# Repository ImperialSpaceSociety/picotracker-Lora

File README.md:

# Pico Ballon Tracker using LoRaWAN

## Objectives
This Pico balloon tracker is a new version to be designed by Imperial College Space Society. It is intended to offer an easy to build and low cost entry for people who want to launch small Helium filled balloons with a small tracking payload while using the Things Network LoRaWAN Network to receive the telemetry data from the balloon.

 implentation objective is to fly a small balloon around the world and to track it using the Things Network and HabHub.

## Major components
We have settled on the following components to go on the tracker solution. 

### Tracker

* Murata ABZ LoRa Module MCU with 868MHz LoRaWAN Radio and 32 Bit ARM CPU
* Ublox Max M8Q GPS module
* MS8607 Pressure temp humidity sensor
* Solar Power Management
* Possible small Energy storage by battery or super capacitor
The moto: KEEP IT SIMPLE

### TTN2HabHub Bridge

* Subscribe to Things Network Application for data from trackers
* Store Tracker data and meta data showing gateway information
* Forward tracking data to HabHub
* Possibly send data back to tracker
The bridge can be found in a seperate repo: [link](https://github.com/ImperialSpaceSociety/ttnhabbridge)

### Launch Gateway

* Portable Things Network LoRaWAN Gateway
* Cellular Internet Access to Things Network
* GPS
* Local Gateway Status Display
* Local Payload Data display

### Balloon

* Low cost 36 inch super pressure balloon
* Prestressed
* Helium Filled

### Tracker Firmware
All firmware used in the trackers can be found here: https://github.com/ImperialSpaceSociety/LoRaMac-node. Its a fork of the Semtech Loramac-node reference firmware.
Note that the code in the current repo is no longer used and is used for reference only.

# Flights
* ICSPACE15: [Flight report](https://www.union.ic.ac.uk/guilds/icseds/2020/01/long-range-lora-balloon-tracker-launch-from-london/)
* ICSPACE16: [Flight report](https://www.union.ic.ac.uk/guilds/icseds/2020/02/balloon-flights-to-austria-and-slovakia/)
* ICSPACE17: [Flight report](https://www.union.ic.ac.uk/guilds/icseds/2020/02/balloon-flights-to-austria-and-slovakia/)
* ICSPACE18: Was lost after launch
* ICSPACE19: [Flight report](https://www.union.ic.ac.uk/guilds/icseds/2020/03/launch-of-icspace19/)
* ICSPACE20 & 21: [Flight report](https://www.union.ic.ac.uk/guilds/icseds/2020/10/icspace21-flight-to-japan-and-icspace20/)
* ICSPACE22: [Flight report](https://www.union.ic.ac.uk/guilds/icseds/2020/12/first-unconfirmed-circumnavigation-of-the-earth-by-ic-space-society-balloon-icspace22/)
* ICSPACE23: [Flight report](https://www.union.ic.ac.uk/guilds/icseds/2020/12/icspace23-launch/)

Past flight paths may be viewed on the [map](https://charts.mongodb.com/charts-project-0-wlibw/public/dashboards/487e7641-c649-4822-abc5-f70eb2e155c7).

# Design Files
The PCBs are designed with Kicad and the latest designs can be found in the [hardware folder](hardware/Kicad/). We have two designs, the a and the b variant. a variant is a fully solar powered tracker with no power storage. The solar cells are directly wired to VCC and GND to power all components. b variant has a 50mAh lipo on board for power storage. The MPPT IC on board, the SPV1040, extracts maximum current from the cells to charge the battery.

As of 29/12/2020, the latest flight proven design is V1.3a. The b variant has not been flown yet.

The schematic of v1.3a is here:

Assembled tracker:

PCB top layer(v1.3a): 

PCB bottom layer(v1.3a):

# Software
We use the KEIL IDE to program the tracker. KEIL can be downloaded and used free of charge for the STM32L0 series of microcontrollers. You will be able to download Keil from [here](https://www2.keil.com/stmicroelectronics-stm32/mdk). Make sure you activate the licence so that you can compile files greater than 30kb of flash. There is no cost for the licence.

We use the ST link to program the STM32L0 microncontroller. You will likely need the ST-link Driver, which can be downloaded from their website: [link]( https://www.st.com/en/development-tools/stsw-link009.html#get-software)

To get the picotracker firmware, run the following to clone the repo. Useful tip: Ensure the repo is cloned to the root folder e.g. `C:\` because there have been issues with the path lengths of the files getting too long for Windows to handle. The repo has very very long paths, a legacy of the LoRaWAN firmware stack by STMicroelectronics.
```bash
git clone https://github.com/ImperialSpaceSociety/picotracker-Lora.git
```
The software on the latest tracker can be found in the [Software folder](Software). You need to navigate to ``Software/Projects/B-L072Z-LRWAN1/Applications/LoRa/End_Node/MDK-ARM/`` and you can open the KEIL project by clicking ``Lora.uvprojx``

Once you open Keil, it should look like this. Ensure that the 1.3a_variant of the code is selected(highlighted in picture): 

You will have to tell Keil that you are using the ST-link programmer. To do that, go to the `flash` drop down menu and select `Configure Flash Tools`. Then switch to the `debug` tab and ensure the drop down menu is set to `St-Link Debugger` as shown in the picture below. Then click the `settings` button.

When you open up the settings menu, it should look like this: 

Now that your st-link debugger is setup, its time to compile and program. Ensure the ST-link programmer is connected to the tracker, and hit compile and then upload or debug. Note: Its necessary to compile before uploading, or it will not have the latest hex file to flash to the tracker.

# Software overview
The picotracker state machine is as follows: 
It gets a GPS fix every 2 minutes and transmits it to ground

### Edits done over the reference version by STMicroelectronics
* Switching LoRaMAC regional settings depending on where it is
* Reduce tx power over US915/AU915
* Prevent sending empty frame after boot
* Use subband of 8 channels for US915/AU915
* Seperate credentials for each region of the world. 
* Prevent sticky uplinks after receiving channel change requests. Actually prevent any uplinks to test channel change requests. Wait till the next scheduled uplink.
* Different datarate for each region
* Polling specific date ranges for eeprom records
* 
# Photos
These are photos of ICSPACE19 before launch, during testing in the sun. It is a 1.1a variant, with no power storage.

# Instructions for special tests of multiregion Lorawan

In this test, I want to test if the tracker will work properly over US915. We have had issues where some packets over Canada contained no payload data. I don't know the root cause. Could be power supply issues. To narrow down causes, I have created this test, to be run on the B-L072Z-LRWAN1.

This test will:
1. transmit every 2 minutes
2. a packet the size of our typical message
3. on US915 frequencies.

I want to find out if we receive any empty packets.

## How to run the program

Clone this project and switch to branch `multi-region-tests`. All tests on multi region lorawan will be here.
Navigate to `picotracker-Lora/Software/Projects/B-L072Z-LRWAN1/Applications/LoRa/End_Node/MDK-ARM/` and run `Lora.uvprojx` with Keil.

After opening the Keil project, switch the firmware config to work on the B-L072Z-LRWAN1 dev board. This can be done as follows: 

Now compile and upload the code into the dev board.

The board will output debug information at `20000000` baud. I normally use the Arduino editor's inbuilt terminal. 

An expected output on the terminal will look like this. It will initialise, and transmit a packet every 2 minutes. This packet will be the same size as the ones transmitted over Canada on ICSPACE22 and will be transmitting on US915 freqencies. This will replicate the same parameters of ICSPACE22 over Canada, where we saw that some packets did not contain any data at all. Note that this program will not need any peripherals(GPS, sensors etc).
```

************************************ 
* Picotracker Lora                 * 
* Imperial College Space Society   * 
************************************ 

SELFTEST: Initialising Hardware
SELFTEST: LED should blink now
SELFTEST: Now initing sensors
SELFTEST: Initialisng ms5607
SELFTEST: Now the radio should transmit
APP DUTY CYCLE(TX INTERVAL maybe longer depending on message length and datarate) : 12000
ABP
DevEui= 00-AB-DF-8A-62-F5-C1-81
DevAdd=  26011673
NwkSKey= D1 21 88 24 49 F6 0C 62 C0 C1 EF 4E FC 24 EC E4
AppSKey= 8F 3C F3 ED 51 FE 03 64 EC 0E 1A 06 6D 41 FC 9D

READING SENSOR AND GPS
================================================================
SENSOR AND GPS VALUES
================================================================
Temperature degrees C: 0.000000
Pressure mBar: 0.000000
Longitude: 0.000000 Latitude: 0.000000 altitude: 0
Solar voltage no load: 3
Solar voltage with GPS load: 0
================================================================
TX on freq 904600000 Hz at DR 4
⸮  1s615ms: PHY txDone
⸮RX on freq 923900000 Hz at DR 13
⸮  2s646ms: PHY rxTimeOut
⸮RX on freq 923300000 Hz at DR 8
⸮  3s698ms: PHY rxTimeOut
  3s707ms: APP> McpsConfirm STATUS: OK

  3s707ms: #= U/L FRAME 6640 =# Class A, Port 99, data size 26, pwr 2, Channel Mask FF00 

⸮READING SENSOR AND GPS

================================================================
SENSOR AND GPS VALUES
================================================================
Temperature degrees C: 0.000000
Pressure mBar: 0.000000
Longitude: 0.000000 Latitude: 0.000000 altitude: 0
Solar voltage no load: 3
Solar voltage with GPS load: 0
================================================================
TX on freq 904600000 Hz at DR 4
⸮ 13s642ms: PHY txDone
⸮RX on freq 923900000 Hz at DR 13
⸮ 14s673ms: PHY rxTimeOut
⸮RX on freq 923300000 Hz at DR 8
⸮ 15s726ms: PHY rxTimeOut
 15s735ms: APP> McpsConfirm STATUS: OK

 15s735ms: #= U/L FRAME 6641 =# Class A, Port 99, data size 26, pwr 2, Channel Mask FF00 
```
### Speed up debugging tips
If you want to speed up the process for debugging, in `main.h`, you can set `APP_TX_DUTYCYCLE` to a lower value to increase the frequency of transmissions.
```c
#define APP_TX_DUTYCYCLE                           120000
```

For debugging, you can switch the end node to transmit on EU868 frequencies by making the following changes to `geofence.c`
```c
LoRaMacRegion_t current_loramac_region = LORAMAC_REGION_EU868;  // Loramac region EU868
Polygon_t curr_poly_region = EU863870_EUROPE_polygon; // Europe is in this polygon
```

### Verify the data(the actual test)
Now if everything is working on the end node side, it is time to see what is appearing on the TTN console. 
You should be able to see packets of data that look something like this. The important thing is, in order to pass this test, every packet should have a `payload_raw` and `payload_fields` section. During ICSPACE22's flight over Canada, we found that some packets did not contain the `payload_fields` section. I want to find out if it is a software issue that causes it.

Note, that every single piece of MQTT data is archived [here](http://medadnewman.co.uk/wp-content/uploads/2020/10/mqtt_log_data-1.txt) for reference. 
```json
{
  "app_id": "icss_lora_tracker",
  "dev_id": "icspace23",
  "hardware_serial": "0093BECA9134091B",
  "port": 99,
  "counter": 6603,
  "payload_raw": "AHN2YwFnERICiAAAAAAAAAAAAAMCAAAEAQA=",
  "payload_fields": {
    "analog_in_3": 0,
    "barometric_pressure_0": 3030.7,
    "digital_out_4": 0,
    "gps_2": {
      "altitude": 0,
      "latitude": 0,
      "longitude": 0
    },
    "temperature_1": 437
  },
  "metadata": {
    "time": "2020-11-06T22:20:03.034197954Z",
    "frequency": 868.5,
    "modulation": "LORA",
    "data_rate": "SF8BW125",
    "airtime": 154112000,
    "coding_rate": "4/5",
    "gateways": [
      {
        "gtw_id": "eui-58a0cbfffe800f4d",
        "timestamp": 3440028508,
        "time": "2020-11-06T22:20:03.082736968Z",
        "channel": 0,
        "rssi": -67,
        "snr": 8.5,
        "rf_chain": 0
      }
    ]
  }
}

```

## License

Hardware is Licensed under CERN OHL v.1.2 or later https://www.ohwr.org/documents/294 No warranty is provided for this documentation implied or otherwise.

Software is licensed under MIT License.

MIT License

Copyright (c) 2018 Imperial College Space Society

Derived Software  Copyright (c) 2014  Richard Meadows <richardeoin>

Permission is hereby granted, free of charge, to any person obtaining a copy of this software and associated documentation files (the "Software"), to deal in the Software without restriction, including without limitation the rights to use, copy, modify, merge, publish, distribute, sublicense, and/or sell copies of the Software, and to permit persons to whom the Software is furnished to do so, subject to the following conditions:

Update README.md with minimal ethics#1

What about the application of the Solomonoff induction
to the RF sensing of human brain?
https://en.wikipedia.org/wiki/Talk:Solomonoff%27s_theory_of_inductive_inference

1. If we assume that the algorithmic complexity
of neural processes is relatively small
(you could take a look at the Potapov monography
for some arguments)

2. As far as I know a lot of neural processes in human brain are electric (or electro-chemistry)
in nature. They have a little power and a small
frequency (~ 1-1000 Hz).
So they emit very low frequency radio waves.

3. You can detect those radio waves on
small antennas if the impedance of such antennas
is matched. This is basically the citation
from the book on electrodynamics.
I uploaded one such book on Twirpix site.

4. So you can create a lot of such receivers
- microstrip filter to filter very high frequencies
- impedance matched microstrip antenna
- resistor for noise for oversampling
- very fast comparator to sample signal
in a very large array on a chip using
standard CMOS or some sort of full-custom process
(maybe even with some new materials)

5. BreamForming and large arrays of digital correlators with sub-mm positioning accuracy
could be achived.

so it seems there is no theoretical
obstacles to implement some sort of
RF human brain sensing or even control
if you can implement reverse structure
with array of a large amount of RF amplifiers
with sub-mm beam forming accuracy

BTW I wrote that remark:
https://en.wikipedia.org/wiki/Talk:Solomonoff%27s_theory_of_inductive_inference

What about the application of the Solomonoff induction to the person to person information exchange?

It seems the minimum description length principle could be used to deduce minimum ethics. At least you can compare ethics by the length. What about the following question: how to shoot met-art girl in the dark underground? ~2026-24709-41 (talk) 16:43, 8 June 2026 (UTC)

at least we can ask a question: does russian met-art model from a pic want some money?
and what obstacles do that guess so hard?
why it is so hard to contact her directly?
she lose money, interesting person lose opportunity to make some photos.

also, it seems the economy without coordination primitives based on physics or mathematics
like gold or maybe Bitcoin or maybe some sort of other physical objects or processes
is just a chaos.
Economic calculation based on fiat money is impossible just from scientific methodology
https://en.wikipedia.org/wiki/Talk:Solomonoff%27s_theory_of_inductive_inference

https://transitional-writes.dreamwidth.org/44972.html
Kirill Abramovich aka wieker @ linux.org.ru
Samara, Russia

and the most important question:
what about the minimal ethics deduced from the MDL principle?
is it exist?

what was the obstacle between russian met-art girls and engineers?

The above copyright notice and this permission notice shall be included in all copies or substantial portions of the Software.

THE SOFTWARE IS PROVIDED "AS IS", WITHOUT WARRANTY OF ANY KIND, EXPRESS OR IMPLIED, INCLUDING BUT NOT LIMITED TO THE WARRANTIES OF MERCHANTABILITY, FITNESS FOR A PARTICULAR PURPOSE AND NONINFRINGEMENT. IN NO EVENT SHALL THE AUTHORS OR COPYRIGHT HOLDERS BE LIABLE FOR ANY CLAIM, DAMAGES OR OTHER LIABILITY, WHETHER IN AN ACTION OF CONTRACT, TORT OR OTHERWISE, ARISING FROM, OUT OF OR IN CONNECTION WITH THE SOFTWARE OR THE USE OR OTHER DEALINGS IN THE SOFTWARE.

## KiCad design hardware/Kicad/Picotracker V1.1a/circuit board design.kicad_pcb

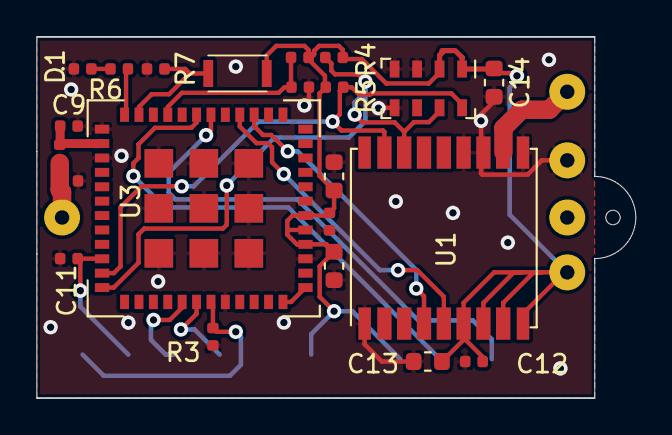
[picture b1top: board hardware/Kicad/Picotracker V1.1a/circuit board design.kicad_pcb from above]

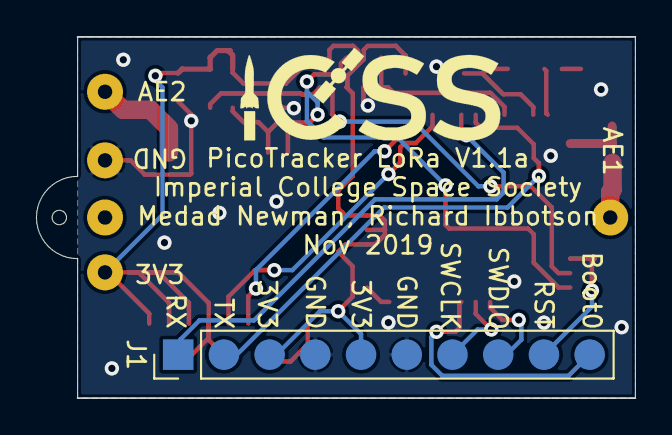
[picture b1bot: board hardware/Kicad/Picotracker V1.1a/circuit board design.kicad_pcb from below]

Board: 2 copper layers, 33.3 x 20.1 mm, 30 parts (2 on the bottom side), 20 nets.

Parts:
AE1: Lora Antenna; SolderWirePad_1x01_Drill0.8mm
AE2: GPS Antenna; SolderWirePad_1x01_Drill0.8mm
C1, C5, C12: 100nF; C_0402_1005Metric
C7: 1uF; C_0603_1608Metric
C9, C11: NF; C_0402_1005Metric
C10, C13: 10uF; C_0603_1608Metric
C14: 220nF; C_0603_1608Metric
D1: LED; LED_0402_1005Metric
J1: Conn_01x09; 10Pad
J2: GND; SolderWirePad_1x01_Drill0.8mm
J3: 3.3V; SolderWirePad_1x01_Drill0.8mm
J4: ICSS Logo; ICSS_Logo
L1: NF; C_0402_1005Metric
R1, R2, R7: 100K; R_0402_1005Metric
R3: 10K; R_0402_1005Metric
R4, R5: 4.7K; R_0402_1005Metric
R6: R; R_0402_1005Metric
SW1: SW_Push; EVPAWCD4A
SolarCellMount1: Unconnected; SolderWirePad_1x01_Drill0.8mm
StringHole1: Unconnected; SolderWirePad_1x01_Drill0.8mm
U1: MAX-M8C; ublox_MAX
U3: CMWX1ZZABZ-078; CMWX1ZZABZ
U6: MS5607-02BA; LGA-8_3x5mm_P1.25mm

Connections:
+3V3: C5.1, C7.1, C10.1, C12.1, C13.1, C14.1, J1.3, J1.5, J3.1, R1.1, R4.1, R5.1, SW1.2, U1.6, U1.7, U1.8, U1.9, U3.4, U3.5, U3.6, U6.1, U6.2
/BOOT0: J1.10, R3.1, U3.43
/GPS_EXTINT: U1.5, U3.16
/GPS_TIMEPULSE: U1.4, U3.15
/I2C1_SCL: R5.2, U1.17, U3.35, U6.8
/I2C1_SDA: R4.2, U1.16, U3.36, U6.7
/LED: R6.2, U3.24
/RESET: C1.1, J1.9, U3.34
/SWCLK: J1.7, U3.42
/SWDIO: J1.8, U3.41
/SWITCH: R7.1, SW1.1, U3.23
/TCXO_EN: U3.1, U3.48
/USART1_RX: J1.1, U3.18
/USART1_TX: J1.2, U3.19
/V_SOLAR: R1.2, R2.1, U3.21
GND: C1.2, C5.2, C7.2, C9.2, C10.2, C11.2, C12.2, C13.2, C14.2, D1.1, J1.4, J1.6, J2.1, R2.2, R3.2, R7.2, U1.1, U1.10, U1.12, U1.13, U3.3, U3.7, U3.25, U3.27, U3.44, U3.49, U3.50, U3.51, U3.52, U3.53, U3.54, U3.55, U3.56, U3.57, U6.3, U6.4, U6.5
unnamed: AE1.1, C11.1, L1.1
unnamed: AE2.1, U1.11
unnamed: C9.1, L1.2, U3.26
unnamed: D1.2, R6.1

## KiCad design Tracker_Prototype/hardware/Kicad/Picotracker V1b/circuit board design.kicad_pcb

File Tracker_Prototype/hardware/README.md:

## TODO
* set up circuit to measure solar voltage
* verify if gps circuit is correct
* layout the PCB

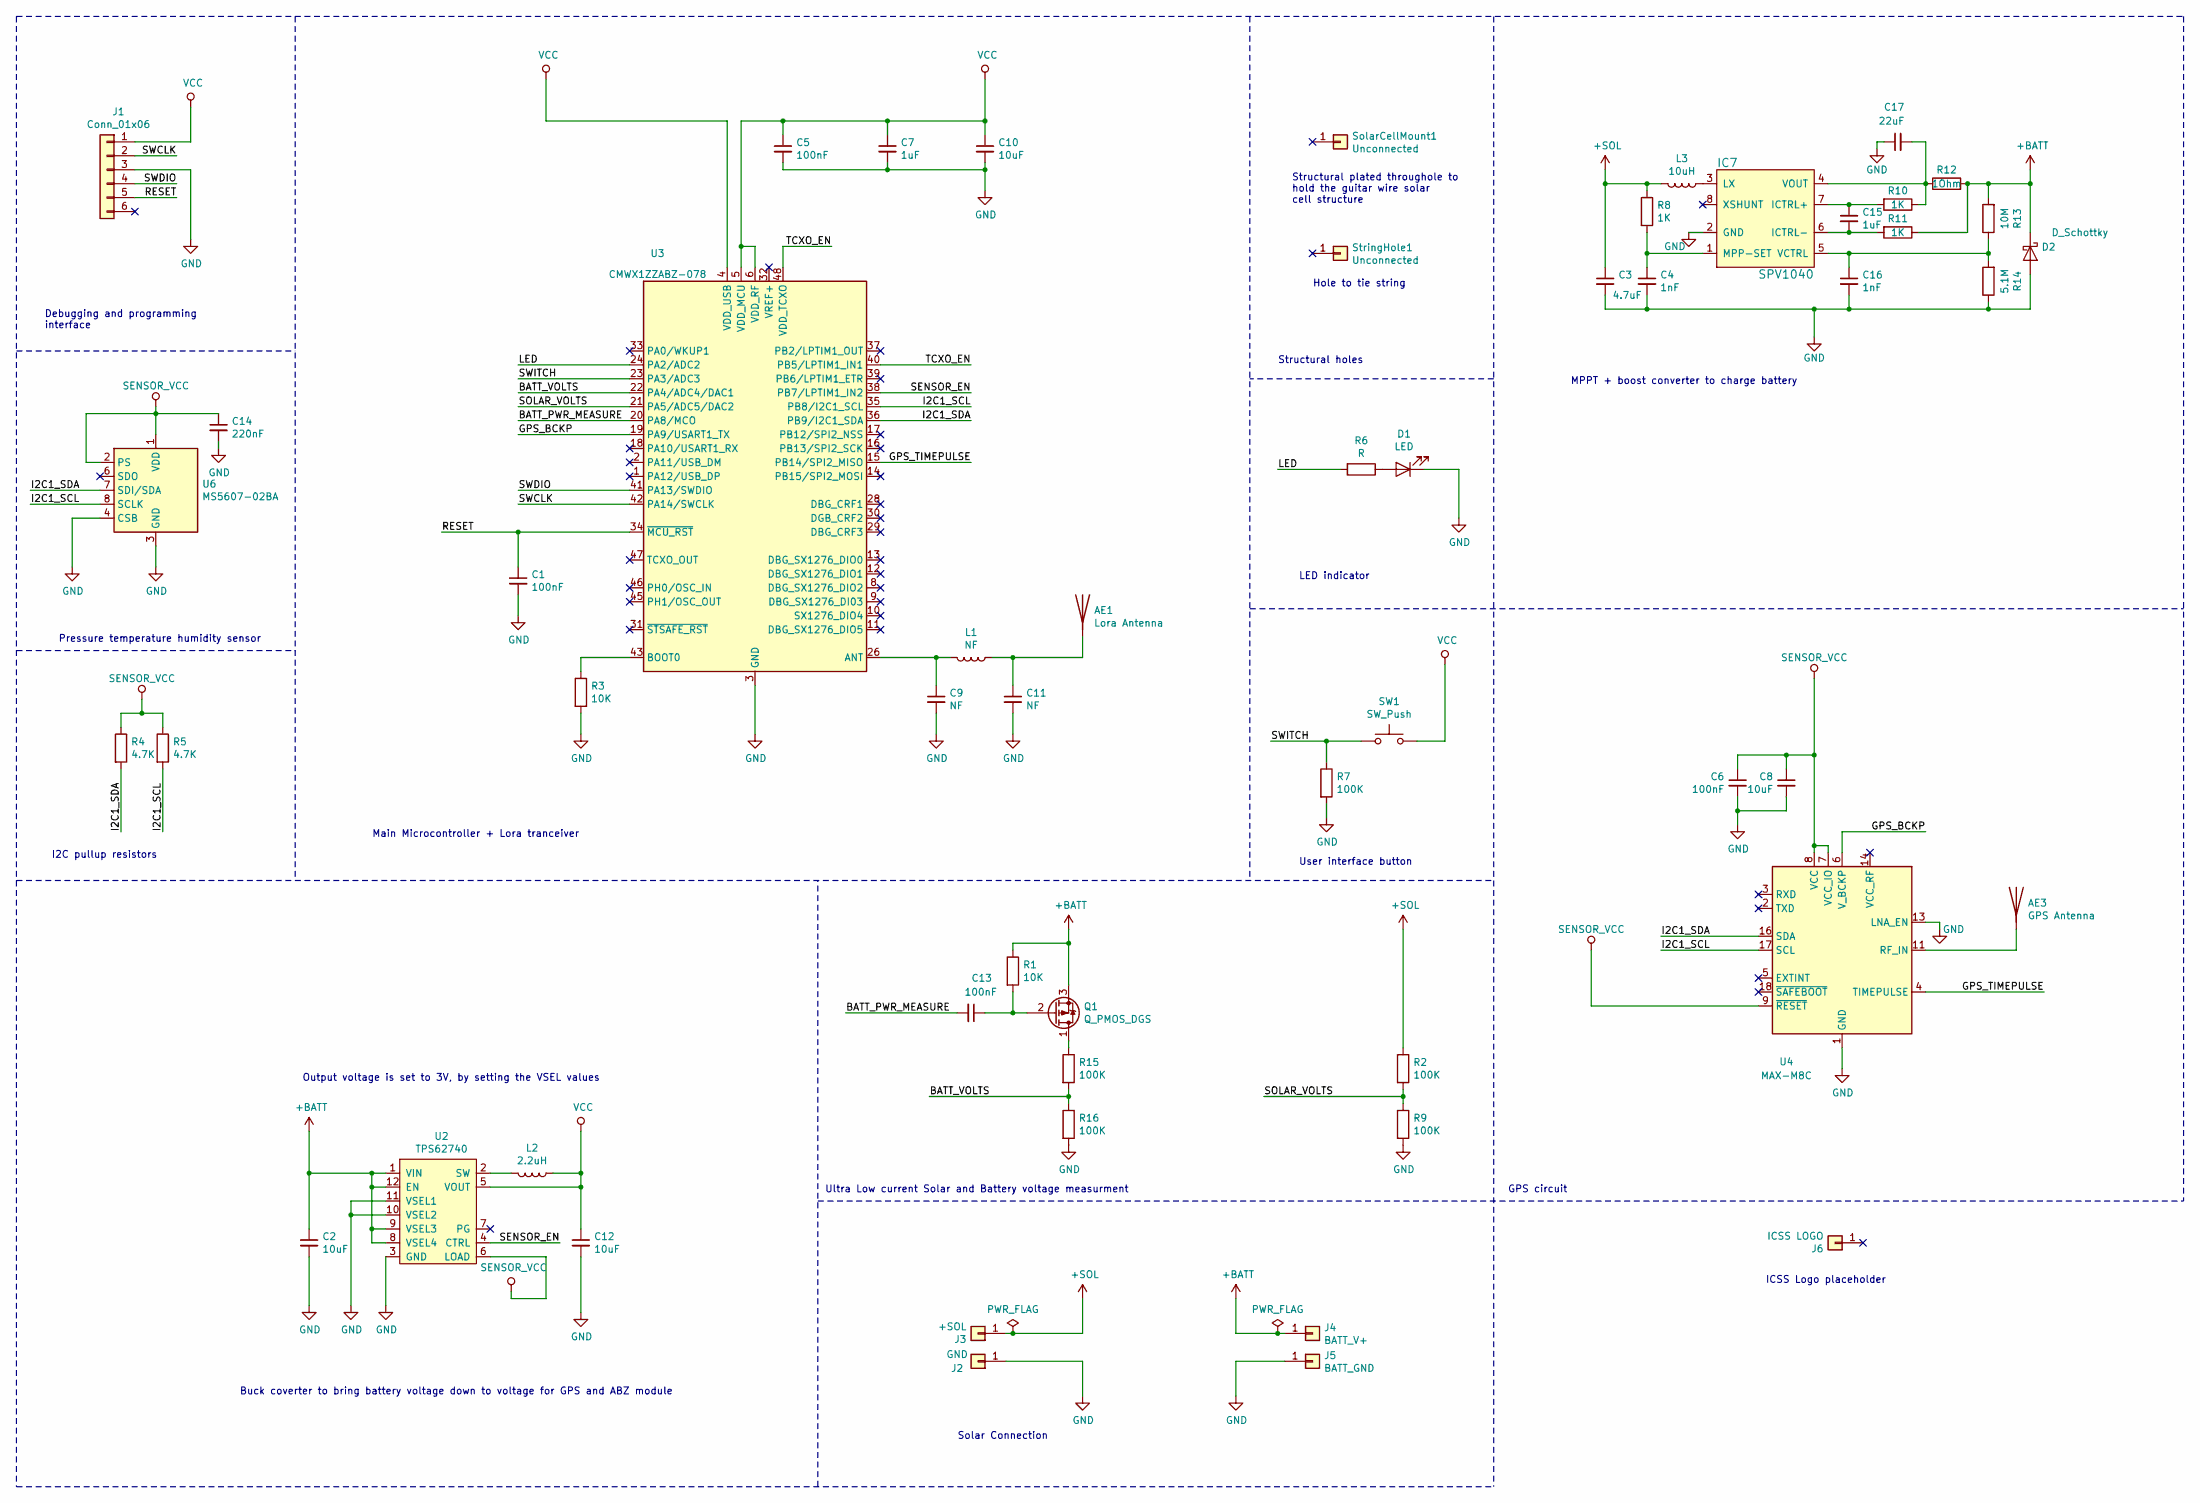
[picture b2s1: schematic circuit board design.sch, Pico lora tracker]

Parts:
AE1: Lora Antenna; SolderWirePad_1x01_Drill0.8mm
AE3: GPS Antenna; SolderWirePad_1x01_Drill0.8mm
C1, C5, C6, C13: 100nF; C_0402_1005Metric
C2, C8, C10, C12: 10uF; C_0603_1608Metric
C3: 4.7uF; C_0805_2012Metric
C4, C16: 1nF; C_0402_1005Metric
C7, C15: 1uF; C_0603_1608Metric
C9, C11: NF; C_0402_1005Metric
C14: 220nF; C_0603_1608Metric
C17: 22uF; C_0805_2012Metric
D1: LED; LED_0402_1005Metric
D2: D_Schottky; D_0402_1005Metric
IC7: SPV1040; TSSOP-8_4.4x3mm_P0.65mm
J1: Conn_01x06; special_test_pads
J2: GND; SolderWirePad_1x01_Drill0.8mm
J3: +SOL; SolderWirePad_1x01_Drill0.8mm
J4: BATT_V+; SolderWirePad_1x01_Drill0.8mm
J5: BATT_GND; SolderWirePad_1x01_Drill0.8mm
J6: ICSS LOGO; ICSS_Logo
L1: NF; C_0402_1005Metric
L2: 2.2uH; L_Coilcraft_LPS3015
L3: 10uH; L_Coilcraft_LPS3015
Q1: Q_PMOS_DGS; SOT-23
R1, R3: 10K; R_0402_1005Metric
R2, R7, R9, R15, R16: 100K; R_0402_1005Metric
R4, R5: 4.7K; R_0402_1005Metric
R6: R; R_0402_1005Metric
R8, R10, R11: 1K; R_0402_1005Metric
R12: 1Ohm; R_0402_1005Metric
R13: 10M; R_0402_1005Metric
R14: 5.1M; R_0402_1005Metric
SW1: SW_Push; EVPAWCD4A
SolarCellMount1: Unconnected; SolderWirePad_1x01_Drill0.8mm
StringHole1: Unconnected; SolderWirePad_1x01_Drill0.8mm
U2: TPS62740; WSON-12-1EP_3x2mm_P0.5mm_EP1x2.65
U3: CMWX1ZZABZ-078; CMWX1ZZABZ
U4: MAX-M8C; ublox_MAX
U6: MS5607-02BA; LGA-8_3x5mm_P1.25mm

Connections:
+BATT: C2.1, D2.1 (K), J4.1, Q1.3 (S), R1.1, R11.1, R12.2, R13.2, U2.1 (VIN), U2.8 (VSEL4), U2.9 (VSEL3), U2.12 (EN); also elsewhere on the board
+SOL: C3.1, J3.1, L3.2, R2.1, R8.1; also elsewhere on the board
/BATT_PWR_MEASURE: C13.2, U3.20 (PA8/MCO)
/BATT_VOLTS: R15.2, R16.1, U3.22 (PA4/ADC4/DAC1)
/GPS_BCKP: U3.19 (PA9/USART1_TX), U4.6 (V_BCKP)
/GPS_TIMEPULSE: U3.15 (PB14/SPI2_MISO), U4.4 (TIMEPULSE)
/I2C1_SCL: R5.2, U3.35 (PB8/I2C1_SCL), U4.17 (SCL), U6.8 (SCLK)
/I2C1_SDA: R4.2, U3.36 (PB9/I2C1_SDA), U4.16 (SDA), U6.7 (SDI/SDA)
/LED: R6.2, U3.24 (PA2/ADC2)
/RESET: C1.1, J1.5, U3.34 (~MCU_RST)
/SENSOR_EN: U2.4 (CTRL), U3.38 (PB7/LPTIM1_IN2)
/SOLAR_VOLTS: R2.2, R9.1, U3.21 (PA5/ADC5/DAC2)
/SWCLK: J1.2, U3.42 (PA14/SWCLK)
/SWDIO: J1.4, U3.41 (PA13/SWDIO)
/SWITCH: R7.1, SW1.1, U3.23 (PA3/ADC3)
/TCXO_EN: U3.40 (PB5/LPTIM1_IN1), U3.48 (VDD_TCXO)
GND: C1.2, C2.2, C3.2, C4.2, C5.2, C6.2, C7.2, C8.2, C9.2, C10.2, C11.2, C12.2, C14.2, C16.2, C17.1, D1.1 (K), D2.2 (A), IC7.2 (GND), J1.3, J2.1, J5.1, R3.2, R7.2, R9.2, R14.1, R16.2, U2.3 (GND), U2.10 (VSEL2), U2.11 (VSEL1), U3.3 (GND), U3.7 (GND), U3.25 (GND), U3.27 (GND), U3.44 (GND), U3.49 (GND), U3.50 (GND), U3.51 (GND), U3.52 (GND), U3.53 (GND), U3.54 (GND), U3.55 (GND), U3.56 (GND), U3.57 (GND), U4.1 (GND), U4.10 (GND), U4.12 (GND), U4.13 (LNA_EN), U6.3 (GND), U6.4 (CSB), U6.5 (CSB); also elsewhere on the board
unnamed: AE1.1, C11.1, L1.1
unnamed: AE3.1, U4.11 (RF_IN)
unnamed: C4.1, IC7.1 (MPP-SET), R8.2
unnamed: C9.1, L1.2, U3.26 (ANT)
unnamed: C13.1, Q1.2 (G), R1.2
unnamed: C15.1, IC7.7 (ICTRL+), R10.2
unnamed: C15.2, IC7.6 (ICTRL-), R11.2
unnamed: C16.1, IC7.5 (VCTRL), R13.1, R14.2
unnamed: C17.2, IC7.4 (VOUT), R10.1, R12.1
unnamed: D1.2 (A), R6.1
unnamed: IC7.3 (LX), L3.1
unnamed: L2.2, U2.2 (SW)
unnamed: Q1.1 (D), R15.1
unnamed: R3.1, U3.43 (BOOT0)
SENSOR_VCC: C6.1, C8.1, C14.1, R4.1, R5.1, U2.6 (LOAD), U4.7 (VCC_IO), U4.8 (VCC), U4.9 (~RESET), U6.1 (VDD), U6.2 (PS)
VCC: C5.1, C7.1, C10.1, C12.1, J1.1, L2.1, SW1.2, U2.5 (VOUT), U3.4 (VDD_USB), U3.5 (VDD_MCU), U3.6 (VDD_RF)

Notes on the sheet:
Debugging and programming interface
Pressure temperature humidity sensor
GPS circuit
Solar Connection
Main Microcontroller + Lora tranceiver
Structural plated throughole to hold the guitar wire solar cell structure
User interface button
LED indicator
Hole to tie string
Structural holes
MPPT + boost converter to charge battery
Buck coverter to bring battery voltage down to voltage for GPS and ABZ module
Ultra Low current Solar and Battery voltage measurment
I2C pullup resistors
ICSS Logo placeholder
Output voltage is set to 3V, by setting the VSEL values

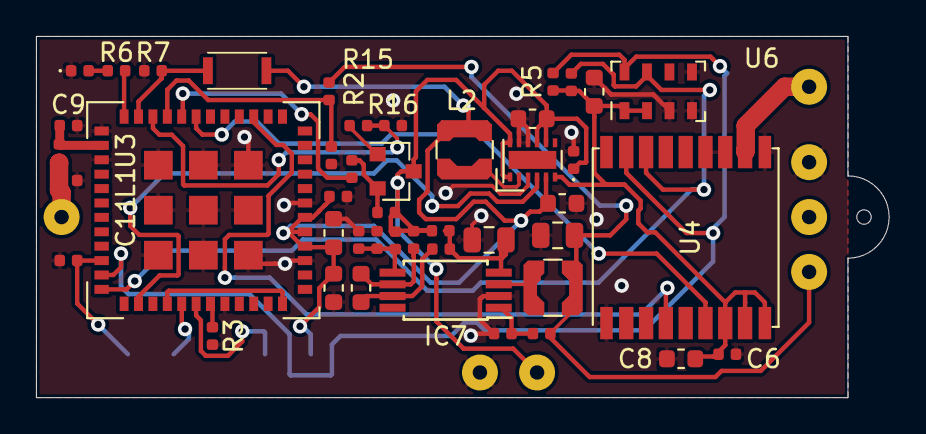
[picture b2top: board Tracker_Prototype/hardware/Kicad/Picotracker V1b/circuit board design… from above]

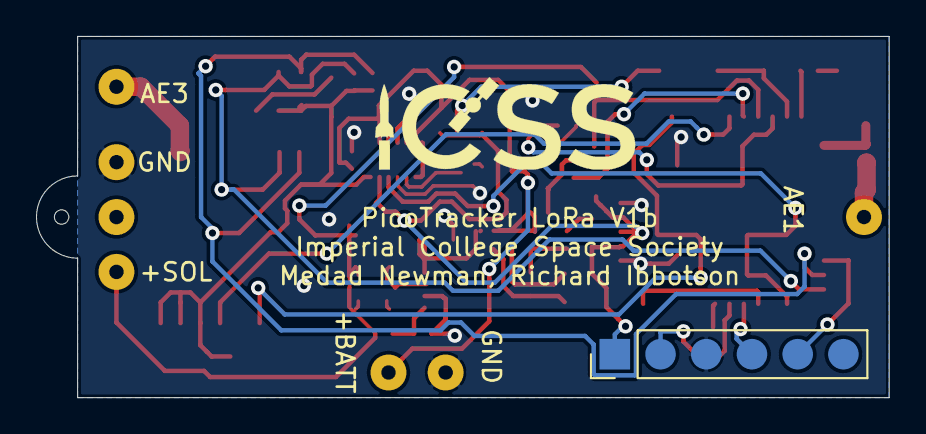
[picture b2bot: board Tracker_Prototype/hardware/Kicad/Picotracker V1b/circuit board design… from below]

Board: 2 copper layers, 47.4 x 20.1 mm, 55 parts (8 on the bottom side), 33 nets.

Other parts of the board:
+BATT: BATT_V+; SolderWirePad_1x01_Drill0.8mm
+SOL: +SOL; SolderWirePad_1x01_Drill0.8mm
GND: BATT_GND; SolderWirePad_1x01_Drill0.8mm
GND#2: GND; SolderWirePad_1x01_Drill0.8mm

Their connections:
+BATT: +BATT.1; also elsewhere on the board
+SOL: +SOL.1; also elsewhere on the board
GND: GND.1, GND#2.1; also elsewhere on the board

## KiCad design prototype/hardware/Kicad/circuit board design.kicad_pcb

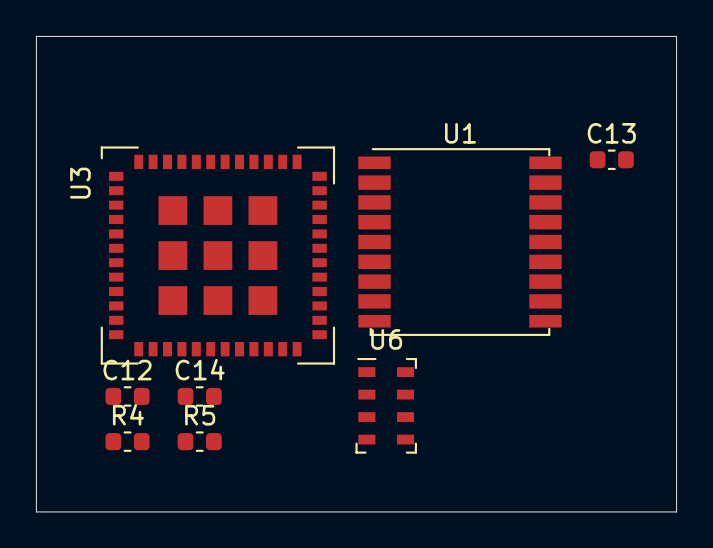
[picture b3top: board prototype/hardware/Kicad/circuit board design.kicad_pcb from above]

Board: 2 copper layers, 35.6 x 26.4 mm, 8 parts (0 on the bottom side), 8 nets, no tracks yet.

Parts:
C12: 100nF; C_0603_1608Metric
C13: 10uF; C_0603_1608Metric
C14: 220nF; C_0603_1608Metric
R4, R5: 4.7K; R_0603_1608Metric
U1: MAX-M8C; ublox_MAX
U3: CMWX1ZZABZ-078; CMWX1ZZABZ
U6: MS5607-02BA; LGA-8_3x5mm_P1.25mm

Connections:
+3V3: C12.1, C13.1, C14.1, R4.1, R5.1, U1.6, U1.7, U1.8, U1.9, U3.4, U3.5, U3.6, U6.1, U6.2
/GPS_EXTINT: U1.5, U3.16
/GPS_SAFEBOOT: U1.18, U3.17
/GPS_TIMEPULSE: U1.4, U3.14
/I2C1_SCL: R5.2, U1.17, U3.35, U6.8
/I2C1_SDA: R4.2, U1.16, U3.36, U6.7
/VDD_TCXO: U3.15, U3.48
GND: C12.2, C13.2, C14.2, U1.1, U1.10, U1.12, U3.3, U3.7, U3.25, U3.27, U3.44, U3.49, U3.50, U3.51, U3.52, U3.53, U3.54, U3.55, U3.56, U3.57, U6.3, U6.4, U6.5

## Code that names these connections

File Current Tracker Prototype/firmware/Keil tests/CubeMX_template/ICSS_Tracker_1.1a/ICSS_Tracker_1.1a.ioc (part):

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Mcu.Name=STM32L072C(B-Z)Yx
Mcu.Package=WLCSP49
Mcu.UserName=STM32L072CZYx
PA1.GPIOParameters=GPIO_Speed,PinState,GPIO_Label
PA1.GPIO_Label=ANT_RX
PA1.GPIO_Speed=GPIO_SPEED_FREQ_HIGH
PA1.PinState=GPIO_PIN_RESET
PA1.Signal=GPIO_Output
PA10.GPIOParameters=GPIO_Label
PA10.GPIO_Label=UART_RX
PA10.Mode=Asynchronous
PA10.Signal=USART1_RX
PA12.GPIOParameters=GPIO_Speed,GPIO_Label
PA12.GPIO_Label=TCXO_EN
PA12.GPIO_Speed=GPIO_SPEED_FREQ_HIGH
PA12.Signal=GPIO_Output
PA13.Mode=Serial_Wire
PA13.Signal=SYS_SWDIO
PA14.Mode=Serial_Wire
PA14.Signal=SYS_SWCLK
PA15.GPIOParameters=GPIO_Speed,GPIO_Label
PA15.GPIO_Label=RA_NSS
PA15.GPIO_Speed=GPIO_SPEED_FREQ_HIGH
PA15.Signal=GPIO_Output
PA2.GPIOParameters=GPIO_Label
PA2.GPIO_Label=LED
PA2.Signal=GPIO_Output
PA3.GPIOParameters=GPIO_Label
PA3.GPIO_Label=BUTTON
PA3.Signal=GPIO_Input
PA5.Mode=IN5
PA5.Signal=ADC_IN5
PA6.GPIOParameters=GPIO_Label
PA6.GPIO_Label=RA_MISO
PA6.Mode=Full_Duplex_Master
PA6.Signal=SPI1_MISO
PA7.GPIOParameters=GPIO_Label
PA7.GPIO_Label=RA_MOSI
PA7.Mode=Full_Duplex_Master
PA7.Signal=SPI1_MOSI
PA9.GPIOParameters=GPIO_Label
PA9.GPIO_Label=UART_TX
PA9.Mode=Asynchronous
PA9.Signal=USART1_TX
PB0.GPIOParameters=GPIO_Label
PB0.GPIO_Label=RA_DIO2
PB0.Signal=GPXTI0
PB1.GPIOParameters=GPIO_Label
PB1.GPIO_Label=RA_DIO1
PB1.Signal=GPXTI1
PB13.GPIOParameters=GPIO_Label
PB13.GPIO_Label=GPS_INT
PB13.Signal=GPIO_Input
PB14.GPIOParameters=GPIO_Label
PB14.GPIO_Label=GPS_PPS
PB14.Signal=GPIO_Input
PB3.GPIOParameters=GPIO_Label
PB3.GPIO_Label=RA_SCK
PB3.Mode=Full_Duplex_Master
PB3.Signal=SPI1_SCK
PB4.GPIOParameters=GPIO_Label
PB4.GPIO_Label=RA_DIO0
PB4.Signal=GPXTI4
PB8.Mode=I2C
PB8.Signal=I2C1_SCL
PB9.Mode=I2C
PB9.Signal=I2C1_SDA
PC0.GPIOParameters=GPIO_Speed,GPIO_Label
PC0.GPIO_Label=RA_RES
PC0.GPIO_Speed=GPIO_SPEED_FREQ_HIGH
PC0.Signal=GPIO_Output
PC1.GPIOParameters=GPIO_Speed,GPIO_Label
PC1.GPIO_Label=ANT_BST
PC1.GPIO_Speed=GPIO_SPEED_FREQ_HIGH
PC1.Signal=GPIO_Output
PC13.GPIOParameters=GPIO_Label
PC13.GPIO_Label=RA_DIO3
PC13.Signal=GPXTI13
PC14-OSC32_IN.Mode=LSE-External-Oscillator
PC14-OSC32_IN.Signal=RCC_OSC32_IN
PC15-OSC32_OUT.Mode=LSE-External-Oscillator
PC15-OSC32_OUT.Signal=RCC_OSC32_OUT
PC2.GPIOParameters=GPIO_Speed,GPIO_Label
PC2.GPIO_Label=ANT_TX
PC2.GPIO_Speed=GPIO_SPEED_FREQ_HIGH
PC2.Signal=GPIO_Output
RCC.HSE_VALUE=8000000
RCC.SYSCLKFreq_VALUE=32000000
RCC.SYSCLKSource=RCC_SYSCLKSOURCE_PLLCLK
board=B-L072Z-LRWAN1
boardIOC=true

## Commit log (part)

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2020-11-21 formatting only
2020-11-21 remove unnecessary code
2020-11-21 refactor function
2020-11-21 do the reset count in bsp. Following, enable GPS
2020-11-21 printout Reset count and data received flag
2020-11-21 move enableing sensor gps to bsp.c
2020-11-21 import main.h
2020-11-21 print out data received from ground
2020-11-21 add in option to use stored lorawan region in EEPROm or not
2020-11-21 refactor read_eeprom_time_pos() to retrieve_eeprom_time_pos()
2020-11-21 move position of function. Formatting only
2020-11-21 remove code repetition
2020-11-21 use mod function when managing overflow of eeprom
2020-11-23 put in corput function
2020-11-23 Revert "use LSI crystal instead of LSE"
    This reverts commit 10a8ec7da5778086a306b6f2c7c6a77101f1cc74.
2020-11-23 make appdutycyle to 20 seconds
2020-11-23 remove redundent #define
2020-11-23 save positoin time to eeprom only every 20 minutes
2020-11-23 print out gps unix time
2020-11-23 put in dummy values for testing
2020-11-23 change default n positoins to send to 12
    Set offset to 0
2020-11-24 move all filling of buffer for tx to playback.c
2020-11-24 part of previous commit
2020-11-24 cleanup lines. rearranged #defines and function prototypes
2020-11-24 send n_playback_postitions_in_eeprom as a pointer
    To dynamically update
2020-11-24 put in corput. Still testing
2020-11-24 update comment
2020-11-24 dont printout out test stuff
2020-11-24 fix odd movment of line, due to version control
2020-11-24 remove completed TODOs
2020-11-24 reduce max subset size
2020-11-24 use more labelled numbers
2020-11-24 removed failed ublox code
2020-11-25 rearrange c and h file
2020-11-25 removed unused todo comment
2020-11-25 don't do redundent calculations
2020-11-25 put in pointer initlialiser during testing
2020-11-25 update test code for playback
2020-11-25 import utilites.h file to the cmake project
2020-11-25 parse playback instructions in main.c
2020-11-25 move location of line
2020-11-25 intialise the corput with a random number
2020-11-25 fix error with scaling for HOW_OFTEN_TO_SAVE_POS_TIM_TO_EEPROM
2020-11-25 remove unused imports
2020-11-25 put in LCG with full cycle of seed value
2020-11-25 make a LGC object
2020-11-25 put in way of tracking number of positions saved since boot
2020-11-25 put in function prototype for converting minute to index
2020-11-25 change APP_TX_DUTYCYCLE to 40s.
    Ensure it no transmission gets blocked
2020-11-25 ensure LGC can handle unexpected data
2020-11-25 fix printout
2020-11-25 update test
2020-11-26 tidy up printout
2020-11-26 send down playback error instead of data received flag
2020-11-26 process incoming isntructions, in bsp.c and playback.c
    seperate them
2020-11-26 put in test to process_playback_instructions
2020-11-26 send 4 byte long for configuring time
2020-11-26 intialise LGC
2020-11-26 save gps success/failure in gps_info struct
2020-11-26 save position time to eeprom only when valid fix
2020-11-26 fix bug in printout
2020-11-27 put in more tests for initing LGC
2020-11-27 get days of data available on eeprom
2020-11-27 select positions from last 500 random set
2020-11-27 dont touch humidity
2020-11-27 Revert "use cleaner implementation for LGC"
    This reverts commit bf9ba7aae55bc211f2b439b9df9d72c4e91a5bf2.
2020-11-28 reduce subset of positions to select from to 400
2020-11-28 put in ICSPACE24 credentials
2020-12-18 rename folder for util scripts python
2020-12-25 save position to eeprom with every fix; (#45)
    increment count only after 20 minutes
2020-12-25 auto format
2020-12-25 optimise imports
2020-12-26 set data rate correctly from init (#48)
2020-12-26 add in a test to test randomness. Passes
2020-12-28 increment counter after 20 minutes, then save
2020-12-28 increment counter after 20 minutes, then save (#51)
2020-12-28 put in the drivers for iwdg
2020-12-28 put in documentation for IWDG
2020-12-28 formating only
2021-01-09 return only when a LGC result is found
2021-01-09 intialise playback with number of positions to select from
    This allows the LGC to select from the last 10 days
2021-01-09 correctly select earliest timepos_index
2021-01-09 refactor n_positions_to_select_from to position_pool_size_to_select_from
2021-01-09 use hardcoded lower value of 0
2021-01-09 remove &n_playback_positions_saved pointer from use
2021-01-09 don't use variable to define DEFAULT_N_POSITIONS_TO_SELECT_FROM
2021-01-09 remove n positoins offset
2021-01-09 update comments to right place
2021-01-09 Revert "ban power saving configs for ublox"
    This reverts commit e9ef4cc4fa53b191b3ca5478ab9719000b76512d.
2021-01-09 Print reset cause (#55)
    * put in reset debug checker
    * move reset debug files
    * add reset debug files to project
    * put in reset case in the main.c
    * catch all reset causes
    * ban power saving configs for ublox
2021-01-09 print out nicely
2021-01-09 put in HAL_IWDG_Refresh in reinit_i2c
2021-01-09 use dynamic datarate depending on region
2021-01-09 send deltas of time from current time. Up to 45 days back
2021-01-09 #52 make it select positions from past n days (#54)
    * return only when a LGC result is found
    * define how long ago to select data from
    * intialise playback with number of positions to select from
    This allows the LGC to select from the last 10 days
    * update comment
    * update comment
2021-01-09 puti n seperate function to playback_hw_init()
2021-01-09 put in seperate function to update reset counts
2021-01-09 add function to pretty print sensor values
2021-01-09 update documentation
2021-01-09 formatting and adding comments
2021-01-09 print normally
2021-01-11 fix casting bug
2021-01-11 memset gps info to all zeros at start of gps search
    Necessary to redefine GPS_FAILURE = 0 because when memsetting all to zero, I want to ensure the default is failure.
2021-01-11 memset gps info to all zeros at start of gps search (#63)
    Necessary to redefine GPS_FAILURE = 0 because when memsetting all to zero, I want to ensure the default is failure.
2021-01-11 print out debug info
2021-01-11 Revert "Update main.h"
    This reverts commit 0898c2070c029d1b4721674434a0c6dc658d41c4.
2021-01-13 update playback days to 15 days from 10
2021-01-15 remove unused parts of repo
2021-01-15 put back csv files that got gitignored
2021-01-15 put back pycharm files
2021-01-15 move hardware folder to root
2021-01-15 Clean up repo (#68)
    * remove unused parts of repo
    * move util scripts
    * put back csv files that got gitignored
    * allow back csv and xml files to be version controlled
    It is too broad,
    * put back pycharm files
2021-02-02 Added in images to readme
2021-02-02 hide overlapping silk screen
2021-02-02 put in test point on GPS pps pin
2021-02-02 analyse logs between transmissions
2021-04-20 pat watchdog every 10 seconds
    Don't pat it every loop around the main loop
2021-04-20 Autoformat ONLY
2021-04-20 Autoformat only (#73)
    * Autoformat ONLY
    * Auto format ONLY
    * Auto format only
2021-04-20 remove redefinition
2021-04-20 don't bother saving geofence location to eeprom on first read again
2021-04-20 move watchdog referesh to better place
2021-04-20 ensure the timer to pat the watchdog timer is initialised
2021-04-20 use function that returns signed temperature reading
2021-04-20 remove all the pointless toggling of the power to gps
    Also remove toggling of scl and sda lines
2021-04-20 remove uncessary function
2021-04-20 never factory reset the gps.
2021-04-20 remove unused functions for i2c pins
2021-04-20 remove unused comments ONLY
2021-04-20 Revert "Auto format only"
    This reverts commit e9b203d2b29576782232648bc8378281234685cc.
2021-04-20 remove all the pointless toggling of the power to gps (#23)
    * remove all the pointless toggling of the power to gps
    Also remove toggling of scl and sda lines
    * remove uncessary function
    * put in i2c error debug message
    * remove all the pointless toggling of the power to gps
    Also remove toggling of scl and sda lines
2021-04-20 allow gps setup time
2021-04-20 Revert "allow gps setup time"
    This reverts commit 9c3a234cf366b20f990b061b9f6b56ca71cf5779.
2021-04-20 Undo gps speedups (#79)
    * Revert "allow gps setup time"
    This reverts commit 9c3a234cf366b20f990b061b9f6b56ca71cf5779.
    * Revert "remove all the pointless toggling of the power to gps (#23)"
    This reverts commit eed6288b24fdbbf9db9de31db993c0a207acc879.
2021-04-20 reuse variable and print temperature
2021-04-27 add options to bsp_sensor_read to select which sensor to read
2021-04-28 Revert "Merge pull request #82 from ImperialSpaceSociety/ensure-it-does-not-send-rubbish-on-first-tx-after-boot"
    This reverts commit e195ceaba68dc01ac17e0bdb45b6abec64d9d036, reversing
    changes made to c496bae3c0ef7b593c40b80a990ebcef2f49b612.
2021-05-03 plot data
2021-05-03 use new file for data
2021-05-03 plot icspace25 data
2021-05-03 reduce minimum altitude
2021-05-03 print more exceptions
2021-05-03 remove useless print
2021-05-03 put raw logs
2021-05-06 switch to icspace26-ttnv3-abp-eu credentials
2021-05-06 increase pool of playback days to 30 days, up from 15 days.
    Eduard YOICT's flight took 25 days to circumnavigate. Its due to summer now.
2021-05-06 Make tracker tx on EU868 over Russia.
    Russia uses EU868 according to https://www.thethingsnetwork.org/docs/lorawan/frequencies-by-country/#r. However, there is conflicting information. Does Russia use its own frequency plan LORAMAC_REGIO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
2021-05-06 fix compile error where Error_handler() function was not found.
    Import the header file for it.
2021-05-08 define geofence_status_t stuct in the h file
2021-05-08 setup files for region settings
2021-05-08 Autoformat lora.c ONLY
2021-05-09 [INCOMPLETE]use region_settings file to set the right LoRaWAN parameters
2021-05-10 create a mocking file to mock LoRaMacRegion_t
2021-05-10 make geofence functions accessible from outside
2021-05-10 AUTOFORMAT geofence_ut only
2021-05-10 create the case switch options and framework for each region network keys
2021-05-10 use function to get network keys
2021-05-10 use #defines for the common keys
2021-05-10 get current network keys and print out.
2021-05-11 format the device id well
2021-05-11 make generate commands for every region
2021-05-11 Updated keys
    Updated for AS923, AU915, CN779, EU868, KR920, IN865, US915. Not done russia
2021-05-11 switch to lorawan-version 1.0.3
2021-05-11 For the special case of the EU868 region, set rx1 to 5 seconds default
2021-05-11 use #define to select whether to set EU RX1 delay to 5 seconds by default
2021-06-09 put in new credentials test-mac-reset-2
2021-06-11 use unique id before device name
2021-06-12 use random hex and date
2021-07-03 don't set rx1 day to 5s by default
    Get the server to send the settings each time
2021-07-03 Revert "put in new credentials test-mac-reset-2"
    This reverts commit f49ee7329d237b47055db42e50759b6e4ff28aab.
2021-07-03 use EU 868 frequency plan that uses SF9 for RX2
2021-07-09 Fix pointless uplinks after boot on TTNv3
    Disable SetMlmeScheduleUplinkIndication(...).
    This uplink is sent until a downlink is sent from server to ack that settings have been successful. However, the TTN server does not send this downlink, and the tracker ends up sending these uplinks 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
    don't save fcount to eeprom
    Restart from zero after each reset, to ensure the server sends up the RX1 delay window settings and channel selection each time.
    don't set rx1 day to 5s by default
    Get the server to send the settings each time
2021-07-27 use correct git link for cpputest
2021-07-27 put in setting for cpputest explorer
    Hardcodes location of executable with absolute path. Not good.
